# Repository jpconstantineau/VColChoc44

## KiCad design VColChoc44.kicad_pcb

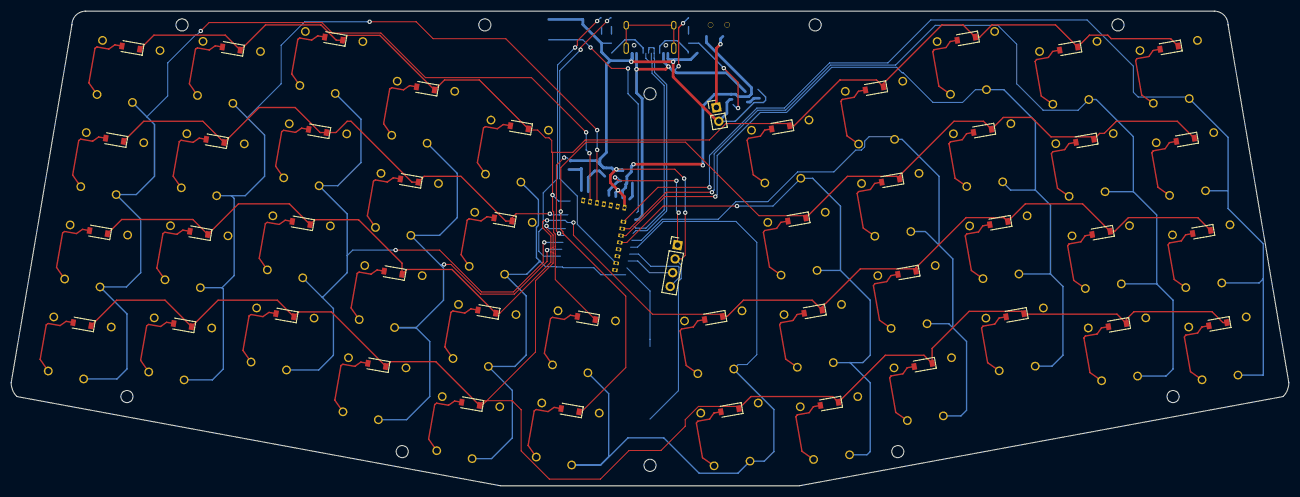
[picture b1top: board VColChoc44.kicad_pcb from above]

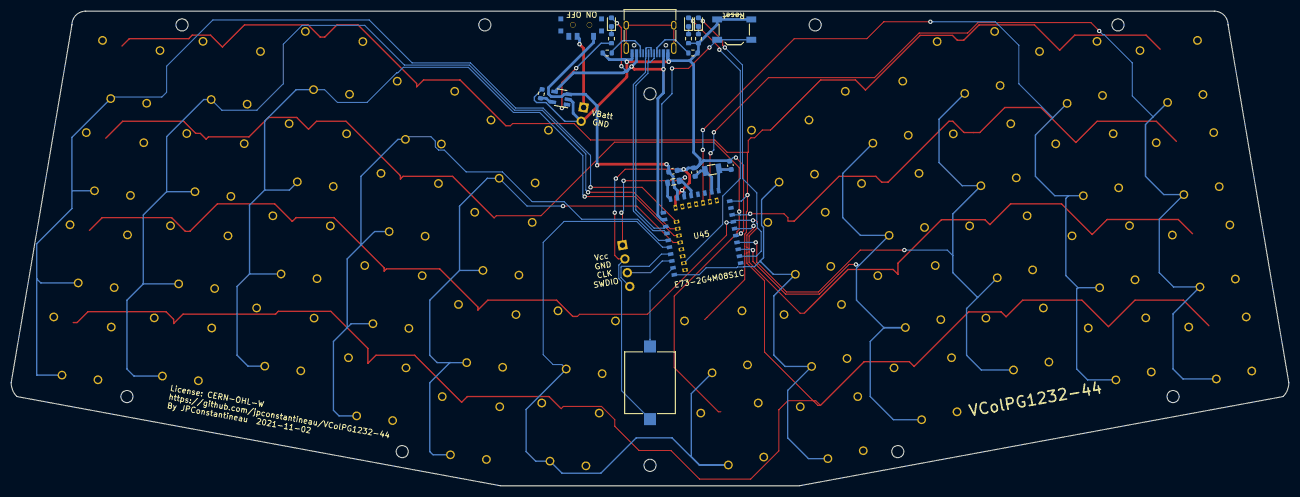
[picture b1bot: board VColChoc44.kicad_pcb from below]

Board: 2 copper layers, 232.1 x 86.2 mm, 76 parts (20 on the bottom side), 38 nets.

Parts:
C1, C2: 22pF; C_0603_1608Metric
C3: 10uF; C_0603_1608Metric
D1: KT-0603R; LED_0603_1608Metric
D2: 19-217/BHC-ZL1M2RY/3T; LED_0603_1608Metric
D3: 19-217/GHC-YR1S2/3T; LED_0603_1608Metric
H1, H2, H3, H4, H5, H6, H7, H8, H9, H10: MountingHole; MountingHole_2.2mm_M2_DIN965
J1: Conn_01x02_Male; PinHeader_1x02_P2.54mm_Vertical
J2: USB_C_Receptacle_USB2.0; USB_C_Receptacle_HRO_TYPE-C-31-M-12
J3: Conn_01x04; PinHeader_1x04_P2.54mm_Vertical
L1: 10uH; L_0805_2012Metric
LS1: Speaker; Buzzer_Mallory_AST1109MLTRQ
R1, R2, R5: 1K; R_0603_1608Metric
R3, R4: 5k1; R_0603_1608Metric
R6: 10K; R_0603_1608Metric
SW1: SW_SPDT; SPDT_C128955
SW2: SW_Push; SW_TACT_ALPS_SKQGABE010
U1, U2, U3, U4, U5, U6, U7, U8, U9, U10, U11, U12, U13, U14, U15, U16, U17, U18, U19, U20, U21, U22, U23, U24, U25, U26, U27, U28, U29, U30, U31, U32, U33, U34, U35, U36, U37, U38, U39, U40, U41, U42, U43, U44: diode-choc; pg1232-D
U45: E73-2G4M08S1C-52840
U46: TP4054; TSOT-23-5
Y1: 32,768; Crystal_SMD_3215-2Pin_3.2x1.5mm

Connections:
+3V3: J3.1, L1.2, U45.19
BLUE_LED: D2.2, U45.2
COL1: U1.1, U12.1, U23.1, U34.1, U45.14
COL2: U2.1, U13.1, U24.1, U35.1, U45.16
COL3: U3.1, U14.1, U25.1, U36.1, U45.4
COL4: U4.1, U15.1, U26.1, U37.1, U45.3
COL5: U5.1, U16.1, U27.1, U38.1, U45.43
COL6: U6.1, U17.1, U28.1, U39.1, U45.35
COL7: U7.1, U18.1, U29.1, U40.1, U45.34
COL8: U8.1, U19.1, U30.1, U41.1, U45.33
COL9: U9.1, U20.1, U31.1, U42.1, U45.32
COL10: U10.1, U21.1, U32.1, U43.1, U45.30
COL11: U11.1, U22.1, U33.1, U44.1, U45.28
DATA+: J2.A6, J2.B6, U45.31
DATA-: J2.A7, J2.B7, U45.29
GND: C1.2, C2.1, C3.2, J1.2, J2.A1, J2.A12, J2.B1, J2.B12, J3.2, LS1.2, R1.2, R2.2, R3.2, R4.2, R6.1, SW2.1, U45.5, U45.21, U45.24, U46.2
unnamed: C1.1, U45.11, Y1.1
unnamed: C2.2, U45.13, Y1.2
unnamed: D1.1, R1.1
unnamed: D2.1, R2.1
unnamed: D3.1, R5.1
unnamed: J1.1, SW1.2
unnamed: J2.A5, R4.1
unnamed: J2.B5, R3.1
unnamed: L1.1, U45.25
unnamed: R5.2, U46.1
unnamed: R6.2, U46.5
RED_LED: D1.2, U45.40
RESET: SW2.2, U45.26
ROW1: U1.2, U2.2, U3.2, U4.2, U5.2, U6.2, U7.2, U8.2, U9.2, U10.2, U11.2, U45.10
ROW2: U12.2, U13.2, U14.2, U15.2, U16.2, U17.2, U18.2, U19.2, U20.2, U21.2, U22.2, U45.8
ROW3: U23.2, U24.2, U25.2, U26.2, U27.2, U28.2, U29.2, U30.2, U31.2, U32.2, U33.2, U45.7
ROW4: U34.2, U35.2, U36.2, U37.2, U38.2, U39.2, U40.2, U41.2, U42.2, U43.2, U44.2, U45.6
SPEAKER: LS1.1, U45.41
SWCLK: J3.3, U45.39
SWDIO: J3.4, U45.37
VBAT: C3.1, SW1.1, U45.23, U46.3
VBUS: D3.2, J2.A4, J2.A9, J2.B4, J2.B9, U45.27, U46.4

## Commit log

2023-09-05 initial
2023-09-05 added readme

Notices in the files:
VColChoc44.kicad_pcb:
License: CERN-OHL-W
